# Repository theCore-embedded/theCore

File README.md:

# theCore: C++ Embedded Framework

## Description

theCore is highly configurable and straightforward C++ framework aimed to reduce development efforts for embedded applications.
The main idea of theCore is to make as much as possible in the compile time.
This affects the way how the device drivers and peripherals are represented.
In fact, each driver is the template class that is instantiated with all the dependencies in a distinct type by user of theCore in the compile time.

You can check out more directly in the code of [the SPI driver](platform/stm32/export/aux/spi_bus.hpp) or  [the USART bus](platform/stm32/export/aux/usart_bus.hpp).

The project is at the initial stage. But something is already in there:
- CMake-based build-system
- Dependency management through [nix](https://nixos.org/nix/)
- Unit tests using [CppUTest](http://cpputest.github.io/)
- Filesystem [Petite FAT](http://elm-chan.org/fsw/ff/00index_p.html)
- Thread, allocators, devices abstractions
- Platform-level drivers, the IRQ manager, console, startup code
- Useful libraries
- Doxygen documentation

## Getting started

If you are interested in the simplest, ready-made demo project based on theCore, refer to [the blinky example project](https://github.com/forGGe/theCore-blinky).

You may also check [examples within theCore source tree](examples/).

In order to proceed with theCore itself, start cloning this repository:
```
git clone https://github.com/forGGe/theCore.git
```

After it, run:
```
git submodule update --init --recursive
```

When the code is received, you have to download and install all the dependencies.
The process can take some time.
To make it easier, I’d strongly recommend to download and install `nix`.
The installation guide can be found [on the official website](https://nixos.org/nixos/manual/index.html#ch-installation) or [Domenkozar's blog](https://www.domenkozar.com/2014/01/02/getting-started-with-nix-package-manager/).

After `nix` installation, run:
```bash
nix-shell --pure
...
```

## Examples

Examples reside in the [`examples`](examples) dir. Each example contains instructions how to compile and use the example.

To build all examples at once you can use nix and specially crafted [superproject](examples/CMakeLists.txt).
To do that, [enter the nix shell](#getting-started) and proceed as follows.

```bash
cd examples
mkdir build
cd build
cmake ..
make
```

Resulting binaries will be placed under corresponding directories.
I.e. the [cs43l22 example](examples/cs43l22_audio) if built that way, will be placed under `build/stm32f4_cs43l22_audio-prefix/src/stm32f4_cs43l22_audio-build/` directory.
You can refer to the [external project CMake documetation](https://cmake.org/cmake/help/v3.4/module/ExternalProject.html) and [the superproject CMake list file](examples/CMakeLists.txt) to figure out where binaries will be placed.
Instructions describing how to flash binary onto the device placed in the readme file inside each example.

## Unit tests

theCore's unit tests can be built and run on the host machine.
For this you have to run the nix-shell and trigger a build:

```bash
cd /path/to/the/core
nix-shell . --pure
mkdir build
cd build
cmake ..
make
```

Then, you should run the unit tests:
```bash
ctest . --output-on-failure
```

## On-device tests

theCore comes with tests that can be executed on the device itself.
Refer to [the theCore testing documentation](tests/README.md) to figure out how to build, use and manage on-device theCore tests.
To build all tests, [enter the nix shell](#getting-started) and proceed as follows:

```bash
cd tests
mkdir build
cd build
cmake ..
make
```

## Supported platforms

| Short name | Full name | List of supported MCUs | Path in project |
|-----------|------------|------------------------|-----------------|
| stm32f4xx | STM32 F4 series | STM32F407VG | [stm32 multiplatform](platform/stm32) |
| stm32l1xx | STM32 L1 series | STM32L152RE | [stm32 multiplatform](platform/stm32) |
| tm4c      | Texas Instrument TM4C |TM4C123GH6PM | [platform/tm4c](platform/tm4c) |
| host      | Host platform | - | [platform/host](platform/host) |

## Documentation

The current documentation of theCore is completely stated in the code (as doxygen comments).
To generate the HTML pages from Doxygen is quite enough to run:

```bash
make core_doc
```

in the build directory (see [unit tests section](#unit-tests)).

## License

The source code is distributed under LGPL v3.0 License.

## Contribution & Using

The project is on its very beginning, so any help is more than welcome and highly appreciated.
If you'd like to take a part in the project growth and (or) have any questions – feel free to email me at forgge@gmail.com, leave message at [gitter](https://gitter.im/forGGe/theCore) or simply check out [a list of issues](https://github.com/forGGe/theCore/issues).
If you have any suggestions on theCore improvement or just like it how it is, don’t keep silence! I’ll be happy to read your reviews.

When making pull requests, make sure that code conforms to [theCore code style guide](style.md).

You are welcome to use theCore in your own projects.
If there is something that it’s not enough for this, please let me know via email or open some issues and we will do our best to handle this ASAP.
Good luck!

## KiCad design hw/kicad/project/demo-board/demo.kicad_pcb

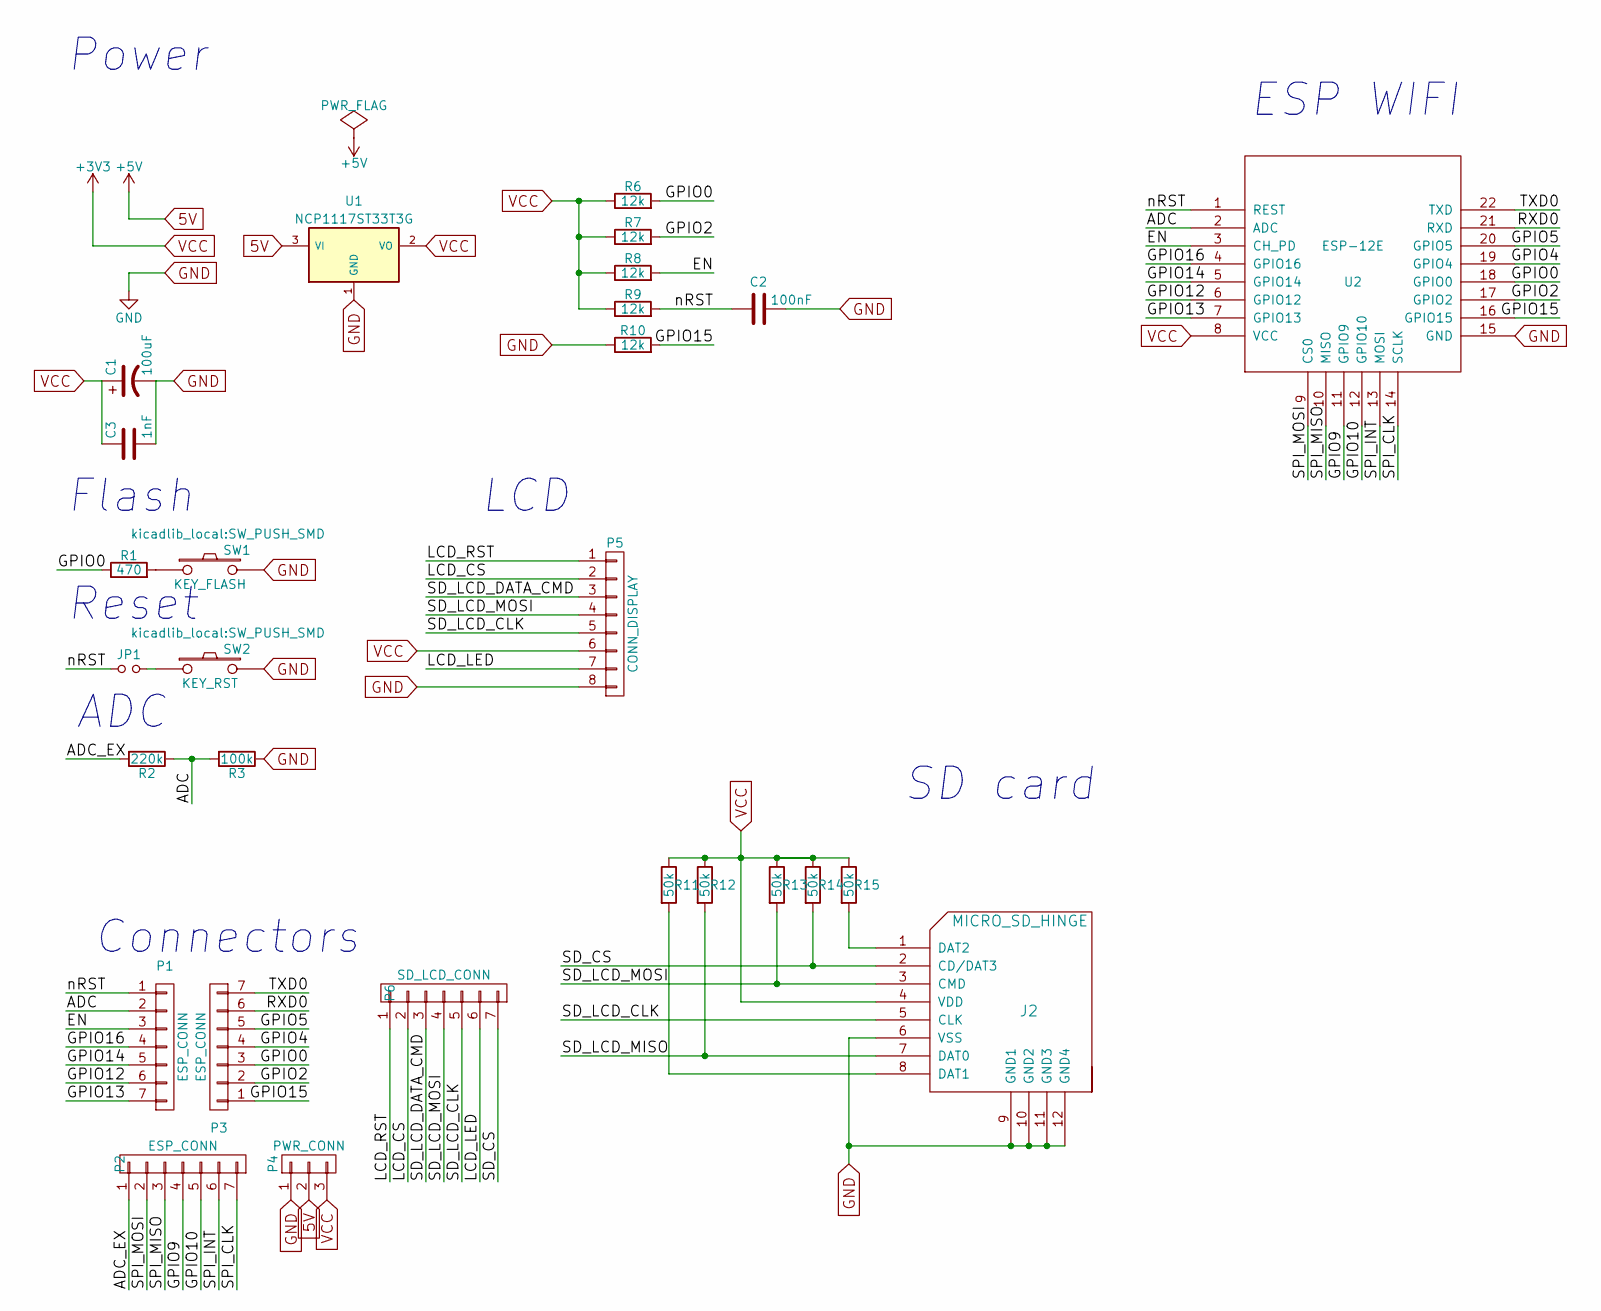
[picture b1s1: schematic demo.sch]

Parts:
C1: 100uF; TantalC_SizeB_EIA-3528_Reflow
C2: 100nF; C_0402
C3: 1nF; C_0402
J2: MICRO_SD_HINGE; MICRO_SD_HINGE_AMP
JP1: Jumper_NO_Small; Pin_Header_Straight_1x02
P1, P2, P3: ESP_CONN; Pin_Header_Straight_1x07
P4: PWR_CONN; Pin_Header_Straight_1x03
P5: CONN_DISPLAY; Nokia_5110_LCD
P6: SD_LCD_CONN; Pin_Header_Straight_1x07
R1: 470; R_1206
R2: 220k; R_1206
R3: 100k; R_1206
R6, R7, R8, R9, R10: 12k; R_1206
R11, R12, R13, R14, R15: 50k; R_1206
SW1: KEY_FLASH; SW_PUSH_SMD
SW2: KEY_RST; SW_PUSH_SMD
U1: NCP1117ST33T3G; SOT-223
U2: ESP-12E; ESP-12E_with_3d

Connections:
5V: P4.2, U1.3 (VI)
/ADC: P1.2, R2.1, R3.2, U2.2 (ADC)
/ADC_EX: P2.1, R2.2
/EN: P1.3, R8.2, U2.3 (CH_PD)
/GPIO0: P3.3, R1.1, R6.2, U2.18 (GPIO0)
/GPIO2: P3.2, R7.2, U2.17 (GPIO2)
/GPIO4: P3.4, U2.19 (GPIO4)
/GPIO5: P3.5, U2.20 (GPIO5)
/GPIO9: P2.4, U2.11 (GPIO9)
/GPIO10: P2.5, U2.12 (GPIO10)
/GPIO12: P1.6, U2.6 (GPIO12)
/GPIO13: P1.7, U2.7 (GPIO13)
/GPIO14: P1.5, U2.5 (GPIO14)
/GPIO15: P3.1, R10.2, U2.16 (GPIO15)
/GPIO16: P1.4, U2.4 (GPIO16)
/LCD_CS: P5.2, P6.2
/LCD_LED: P5.7, P6.6
/LCD_RST: P5.1, P6.1
/RXD0: P3.6, U2.21 (RXD)
/SD_CS: J2.2 (CD/DAT3), P6.7, R14.2
/SD_LCD_CLK: J2.5 (CLK), P5.5, P6.5
/SD_LCD_DATA_CMD: P5.3, P6.3
/SD_LCD_MISO: J2.7 (DAT0), R12.2
/SD_LCD_MOSI: J2.3 (CMD), P5.4, P6.4, R13.2
/SPI_CLK: P2.7, U2.14 (SCLK)
/SPI_INT: P2.6, U2.13 (MOSI)
/SPI_MISO: P2.3, U2.10 (MISO)
/SPI_MOSI: P2.2, U2.9 (CS0)
/TXD0: P3.7, U2.22 (TXD)
/nRST: C2.1, JP1.1, P1.1, R9.2, U2.1 (REST)
GND: C1.2, C2.2, C3.2, J2.6 (VSS), J2.9 (GND1), J2.10 (GND2), J2.11 (GND3), J2.12 (GND4), P4.1, P5.8, R3.1, R10.1, SW1.2, SW2.2, U1.1 (GND), U2.15 (GND)
unnamed: J2.1 (DAT2), R15.2
unnamed: J2.8 (DAT1), R11.2
unnamed: JP1.2, SW2.1
unnamed: R1.2, SW1.1
VCC: C1.1, C3.1, J2.4 (VDD), P4.3, P5.6, R6.1, R7.1, R8.1, R9.1, R11.1, R12.1, R13.1, R14.1, R15.1, U1.2 (VO), U2.8 (VCC)

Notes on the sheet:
Power
ESP WIFI
Flash
ADC
Reset
Connectors
SD card
LCD

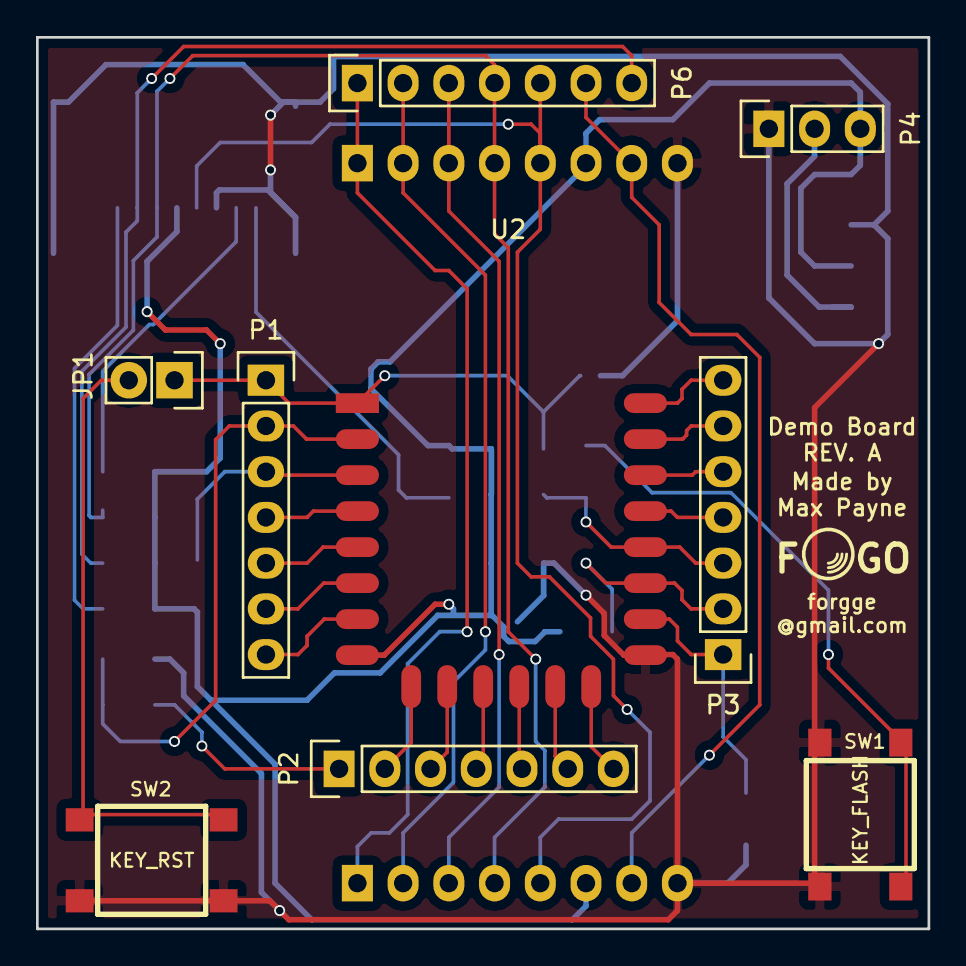
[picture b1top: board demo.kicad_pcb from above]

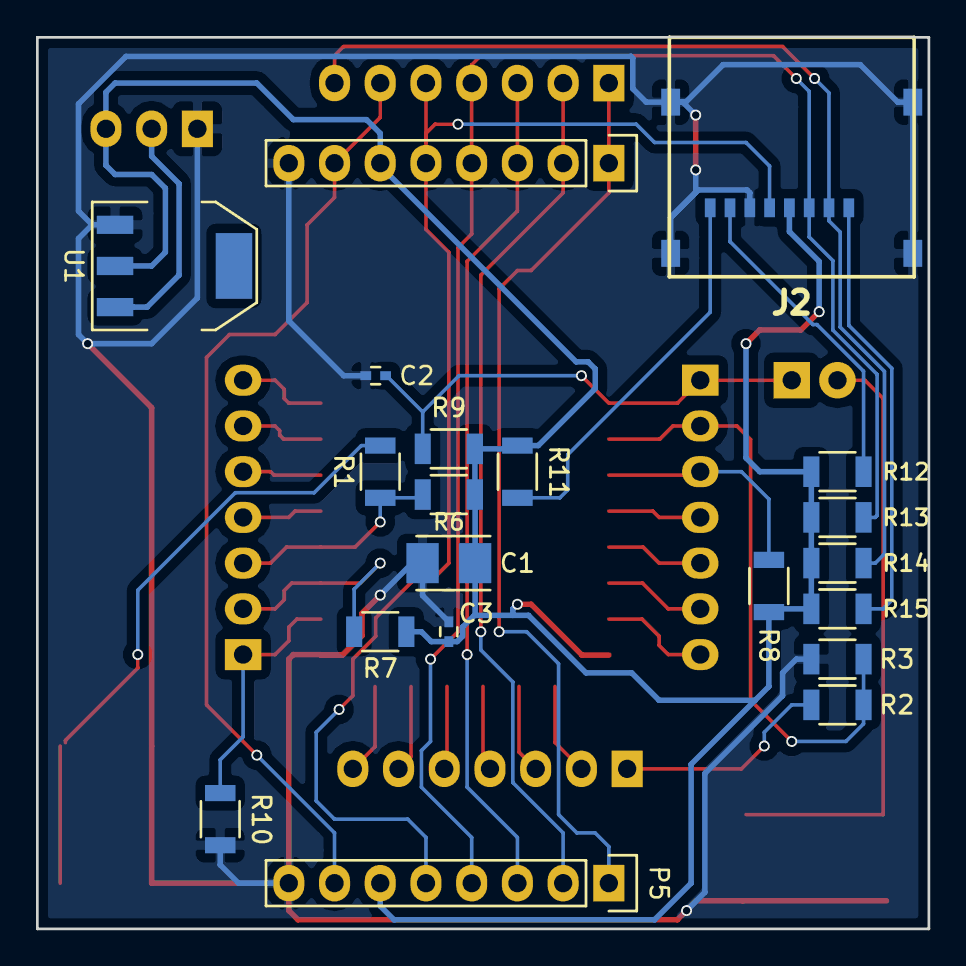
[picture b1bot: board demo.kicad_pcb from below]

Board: 2 copper layers, 49.5 x 49.5 mm, 28 parts (19 on the bottom side), 36 nets.

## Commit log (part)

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2016-08-22 MMIO abstraction unit tests
2016-09-14 Host-only empty test case and test structure improvements
2016-09-18 Add `Hello World` test case stm32f4 discovery configuration
2016-09-18 GCC 6.2 fails to build thread module, workaround for issue #138
2016-09-20 Add functional test helper method in the buildsystem
    Cool shortcut to create new tests
2016-09-20 Implement tm4c skeleton and `empty main` test
2016-09-25 Add Unity demo test case
2016-09-25 Bunch of style fixes for link dependencies
2016-09-27 Unity demo for TivaC board
2016-10-03 Fix double evaluation and indent in linker dispatcher
2016-10-10 Tiva C platform BAT suite
    Contains only GPIO test for now.
2016-10-10 tm4c: gpio and execution headers implementation
2016-10-11 stm32: missing EXTI initiliaztion
2016-10-12 Unity demo and BAT test improvements
2016-10-15 Implement CMake test list generation
2016-10-16 TM4C platform BAT test suite auto-generation
2016-10-18 Add host BAT suite and use bypass console tests
2016-10-23 Specify right autogenerated path for suite runners
2016-10-27 Add tm4c to the board example for flashing script
2016-10-30 tm4c: implement UART init method
2016-11-03 tm4c: make irq modules compatible with TivaWare
    Checks improved as well.
2016-11-06 tm4c: uart fill mode and corresponding test
2016-11-13 stm32 and host: make UART and console drivers work with new interface
2016-11-13 stm32: add USART test to the platform suite
2016-11-14 Fix build issues of pedantic flag in libraries
2016-11-19 stm32: fix incorrect DMA peripheral and memory datasize calculation
2016-11-23 bs: replace CMAKE_FORCE_*_COMPILER with CMAKE_*_COMPILER
    Depreceated CMake macro was removed.
    Reference discussions in cmake-devs:
    http://cmake.3232098.n2.nabble.com/Toolchains-and-CMAKE-FORCE-C-COMPILER-in-3-5-td7592757.html
    https://cmake.org/pipermail/cmake-developers/2016-February/027818.html
    https://cmake.org/gitweb?p=cmake.git;a=commitdiff;h=7f1bd9fe
    Closes #139
2016-11-23 theCore: fix platform selection based on cross-compilation facts
    Proper platform must be set by user if cross-compiling, or it should
    defaulted to `host` if not.
    Closes #136
2016-11-27 Add toolchain support in the test system and clang test suite
2016-11-27 Toolchain file cleanup and CMSIS clang patch
    CLang lacks of understanding what is `vfpcc` register.
    Built-in must be used instead:
    __builtin_arm_set_fpscr(fpscr);
    See also:
    https://codereview.chromium.org/411803002/
    https://chromium.googlesource.com/native_client/src/native_client/+/togit/src/trusted/service_runtime/nacl_syscall_common.c
2016-11-28 Fix UTF BOMs in test case files
2016-12-02 tm4c: fix UART initialization collision in iostream and uart_bat
    Bug similar to #176
2016-12-02 tm4c: verbose test output and EXTI masking policy
    GPIO pad type fixed as well.
2016-12-03 fat: delete PFF files that should go to another submodule
2016-12-04 tests: added theCore test facilities documentation
2016-12-09 theCore: code style guide and formatting script
2016-12-10 Add changelog to theCore
    Autogenerated using https://github.com/skywinder/github-changelog-generator
2016-12-21 stm32: f4 ADC, w/ blocking single-run mode and groupped channels
2016-12-30 >#195 Single-conversion single-channel IRQ mode
    Not yet suitable for conversion of mupliple channels.
2017-01-09 >#172 Soil gygrometer (moisture sensor) analog implementation
    Tests are included
2017-01-15 >#205 Fix build issue in newlib stubs
2017-01-28 >#145 Drop bus dependency when no console is enabled
    Thus, thread library and other utilities are not included.
2017-01-29 >#145 Fix link error of missing mutex dtor
2017-01-30 >#209 Drop CMSIS dependency from TM4C platform
    As it turns out, CMSIS and TM4C driverlib (one that downloaded from TI)
    are incompatible. Multiple re-definition error occur if to try use
    core_cm4.h header along with hw_memmap.h (from driverlib).
    + included new 'execution' platform interface.
2017-01-30 >#209 Improve debug capabilities in unit tests
2017-02-01 >#209 FreeRTOS timed-wait semaphore implementation
    Includes:
    - New suite for stm32 discovery with FreeRTOS enabled
    - Basic test for semaphore
    - Fixes for FPU flags for stm32 platform (linker part) and toolchain
    (compiler part)
2017-02-05 >#207 Xfer cancelation in generic bus
    Platform parts are not there yet, but interface is ready.
2017-02-08 Set theme jekyll-theme-hacker
2017-02-18 >#231 stm32: remove circular mode when listen mode is requested
    Fix UART buffer wraparound.
2017-02-21 KE02 platform files and architecture changes
    Some libraries becomes optional to avoid unnecessary cloning of whole
    submodules set. Architecture module is extended with possibility of
    using NVIC-names interrupts. New startup assembly file is also added.
2017-02-23 >#203 Documentation and tests for HM-10
2017-02-24 >#203 Fix previous listen mode merge and arm-g++ v6.0 warnings
2017-02-26 Add optional flag to disable newlib stubs from theCore
    Applications can override default stubs as well as provide own library
    implementation.
2017-03-05 Kinetis platform console and flash protect support
2017-03-07 >#229 Fix binary semaphore not ignoring excessive events
    Bug was observed during implementattion in #233
2017-03-20 >#72 No-OS semaphores extended with WFI capability
    Namespace fix for execution functions is included
2017-04-01 >#244 Fix excessive TC event in case of listen UART mode
    When listen mode was enabled, UART was generating two transfer-complete
    events on RX channel with the same 'total' count. Second event should be
    removed.
2017-04-02 >#244 Rename spin_wait, add wait_for with predicate argument
    wait_for reflects better internal mechanisms that used during wait.
    Additional argument allows to stop waiting if some condition occur.
2017-04-04 >#244 Fix missing dependency for common module
    Added some notes regarding #246 and small typo change.
2017-05-10 Fix HTU21D compilation errors
2017-05-11 Change 'The Core' to 'theCore'
2017-05-11 >#146 Move error code helper
2017-06-11 >#258 Electron serial RX and console support
    Partially includes fixes for #261.
    - Console is exposed via theCore streams.
    - The platform main loop delay decreased to improve
    character print rate.
    - Enabled RX mode in tests.
2017-06-22 >#258 I2C implementation and finalization in particle platform
    This change includes:
    - Enough complete I2C driver and code generator for it.
    - User-side module that directly included in main object, to prevent
    incorrect linkage.
    - Platform as a separate library to improve compile dependency
    management.
2017-06-25 Added simple led example for TM4C LaunchPadEvaluation board
2017-06-25 >#229 Serial stream skeleton and interface
2017-06-25 >#229 Remove StringFrom() helper function. Fix compilation error with illegal syntax for placement new in safe_storage
2017-06-25 >#229 Review fixes
2017-06-27 >#238 Add colored logs to recent changes in develop
2017-07-02 >#239 JSON-based configuration for stm32 platform
    I2C, I2S, GPIO, ADC and pinmux configuration are avaliable via JSON
    interface. This change is compatible with other platforms that are
    using old interface.
    Tests and examples based on stm32 platform are updated too.
    Configurator is mainly optional. User can re-create any periphery
    configuration in C++.
2017-07-02 Added compiler error check
2017-07-31 Sphinx-based documentation and doxygen fixes
2017-08-21 error time
2017-09-13 >#239 Extract platform configuration into the JSON subobject
    Futher documentation changes will contain detailed explanation.
2017-09-13 >#239 Document JSON configurator and schemas
    During process of documentation building, examples are generated too.
2017-09-13 >#256 Add try_xfer method
2017-09-28 Workaround broken GCC in Nix shell, when clang is used
    Also includes:
    - more performant Nix build (more cores used)
    - suppressed builder output to avoid hitting 4 MB log limit on Travis
2017-09-28 >#282 Prevent unnecessary dependencies to crawl via debug module
2017-09-30 Relicense theCore sources under MPL license
    The project comes under the LGPL3.0+. It could be worthwhile to
    re-license under MPLv2, since it has the SLE (Static Linking Exception)
    baked in and is a standard license.
    It is largely motivated by the embedded industry itself where static
    linkage is a common practice.
2017-10-03 Improve GA, add GA tags to the docuementation
2017-10-05 >#286 Documentation for Particle Electron platform
2017-10-16 >#247 Improve timer build interface and stm32 schemas
    Timer can be now fully given under user control,
    as described in the task.
    Side changes: 'exported_gpio' now named as 'gpio_alias'.
    Examples updated too.
2017-10-17 >#283 TM4C configurator docuemntation and pinmux fix
    Includes minor improvements of documentation layout, typos, etc.
2017-10-22 >309 Cmake-doxygen Nix expression, integration and doxy fixes
    As a result of the integration, many warnings were observed. Now they
    are fixed.
2017-11-05 Fix non-working htu21d example and incorrect docs
2017-11-20 Add more links to doc and main page
    Telegram, mailing list, etc.
2017-11-25 >277 docs: automated deploy script using Travis CI
2017-11-26 >277 Correct bash variable expansion for docs deploy
2017-11-26 stm32: clear error flags during UART transmission
    Uncleared flags forced interrupt storm in case of error
2017-12-03 Change default workdir path and preven doxyfying thirdparties
    Travis configuration tweaked to increase build speeds
2017-12-10 Generate sitemap and add doxygen
2017-12-17 Integrate CMake version4git project + various improvements
2017-12-17 Add missing sources for version4git
2017-12-18 silenced git commit in doc deploy
2017-12-19 automate docker build and push using Travis cron
2017-12-25 Fix clang wrapper issue on Nix
    Essentially, backporting 741ebd93e53f231a
2018-01-15 fix broken links in README
2018-02-11 Split device pages, one page per each device driver
2018-02-13 Reuse generated IRQ for TM4C UART periphery
2018-02-16 Add definition to disable IRQ manager, propagated via platform headers
2018-02-19 add stub example for pcd
2018-02-21 Fix doxygen links and add more files to ignore list
2018-02-23 Implement SPI driver for TM4C platform
    Current driver is limited only to master role and Motorola modes of
    operation.
    "Channel" term is used instead of "device" for recognizing peripherals.
2018-02-25 Change spinlock to mutex in dev/bus and fix TM4C UART BAT
2018-02-26 Implement clock divider for SPI and fix MISO
2018-02-26 Add standart aliases for GPIOs in platform
    In that way, rest of the system can use standart names when refering to
    GPIOs
2018-03-02 Doc improvements: remove unnecessary files from doxygen generation
    Also, couple of fixes added to prettify some pages.
2018-03-02 Add missing theCore schema
2018-03-16 Move voltage profiles to sdspi info struct
2018-03-16 lib/types: add err code to handle EOF condition
2018-03-16 Refactor and re-new FS/FATFS modules
    Includes:
    - r/w capabilities for FATFS abstractions
    - reused new SDSPI interface
    - converted FS main methods to static
    - doxygen and Sphinx documentation
    - unit tests
2018-03-16 git: add junk diff and python files to ignore
2018-03-20 console: renamed bus_pipe -> console_pipe and add echo capability
2018-03-22 Add few words about OpenOCD and NixOS
2018-03-23 Fix source collision when theCore is a part of bigger tree
2018-03-30 Bump cmake-version4git
    Fix wrong calculation of commits number
2018-04-07 ke02: freshen platform and related files
2018-04-07 ke02: add stub example to perform kind-of-a-testing
2018-04-09 ke02: correct initialization and dependencies
2018-04-25 Test commit
2018-05-10 ke02: Fix issues from initial review
2018-05-12 examples: cs43l22 example migrated to new tcore scripts
2018-05-16 docs: merge blinky examples and updated docs
    Moved to: https://github.com/theCore-embedded/example_blinky
2018-05-19 docs: fix sudo command for tcore script
2018-06-14 tm4c: prepare platform to use new configurator
    Old shemas removed. Validation script not needed (yet?).
    theCore ambient CMake files are also fixed, so it means that
    this branch is completely broken for other platforms.
2018-06-24 stm32: use new configurator for the platform
    Includes:
    * relevant documentation changes
    * timer configuration for stm32 ((missing for some reason)
    * merged bupass and regular console
    * SPI configurator (but not generator, yet)
    * pyparse python package for better parsing in generators
2018-06-25 dev: cs43l22 new configurator and docs
2018-06-27 doc, examples: migrate HTU21D example to separate repository
2018-06-30 lib/fs: support new configurator
2018-06-30 doc, examples: migrate fatfs+sdspi example to separate repo
    New configurator support is added as well.
2018-06-30 lib/fs: protect against unnecessary FS module
